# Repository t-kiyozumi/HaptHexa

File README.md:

# HaptHexa
The contents of this repository are the source code and design drawing of a 6-legged robot that can be operated using Dual Shock 3.

#Installation，How to use

Assemble the robot with reference to
HaptHexa / Hardware.

Clone the repository to the computer that controls the robot.

Create a build folder in 
HaptHexa / Software / mainDirectory /

After connecting the dual shock3 controller to the robot's control computer, 
enter the following command to execution

./HaptHexa

Use the left stick to move and the right stick to control the posture.
Pressing select activates the stabilizer and tries to keep the posture horizontal.
In this state, the right stick is used to control the center of gravity.

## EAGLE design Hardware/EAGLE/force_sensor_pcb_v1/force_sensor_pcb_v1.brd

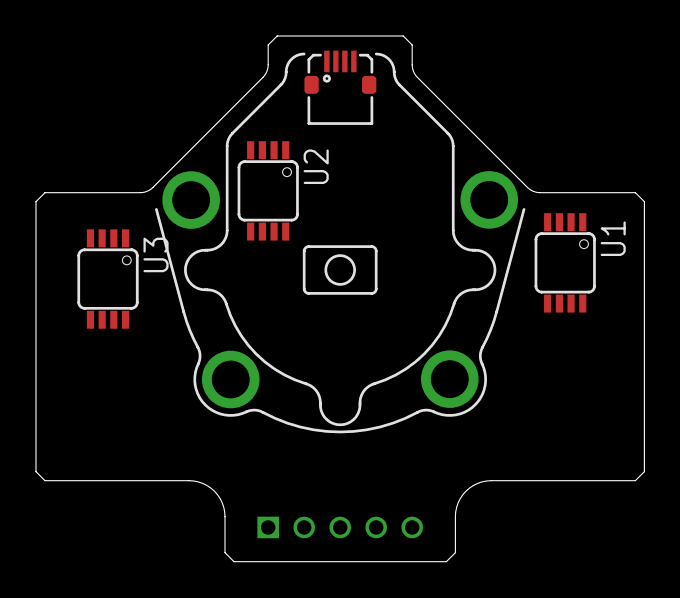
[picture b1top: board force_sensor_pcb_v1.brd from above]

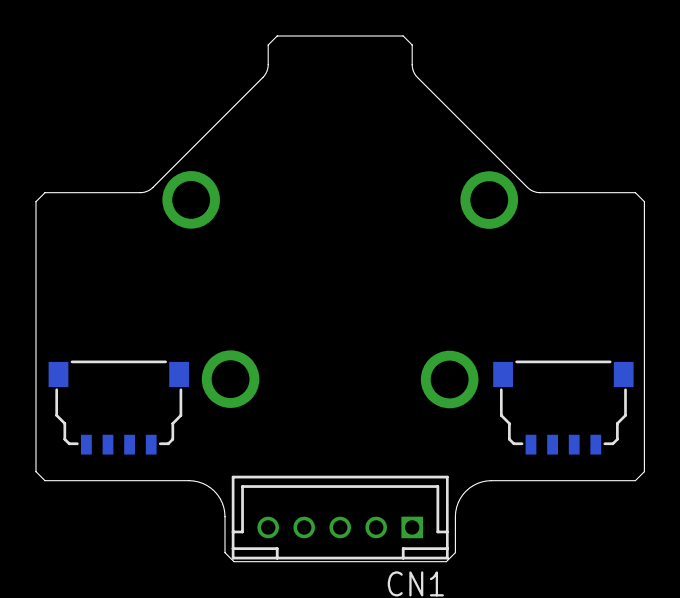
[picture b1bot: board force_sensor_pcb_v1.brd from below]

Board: 2 copper layers, 33.8 x 29.2 mm, 7 parts (3 on the bottom side), 2 nets, no tracks yet.

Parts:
CN1: B5B-PH-K-S
U1, U2, U3: AD623RM-8; MSOP08
U$1: KYOCERA-62774P; KYOCERA-6277-4
U$5, U$6: DF58-4P4P; DF58-4P

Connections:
+V: U1.7, U2.7, U3.7
-V: U1.4, U2.4, U3.4

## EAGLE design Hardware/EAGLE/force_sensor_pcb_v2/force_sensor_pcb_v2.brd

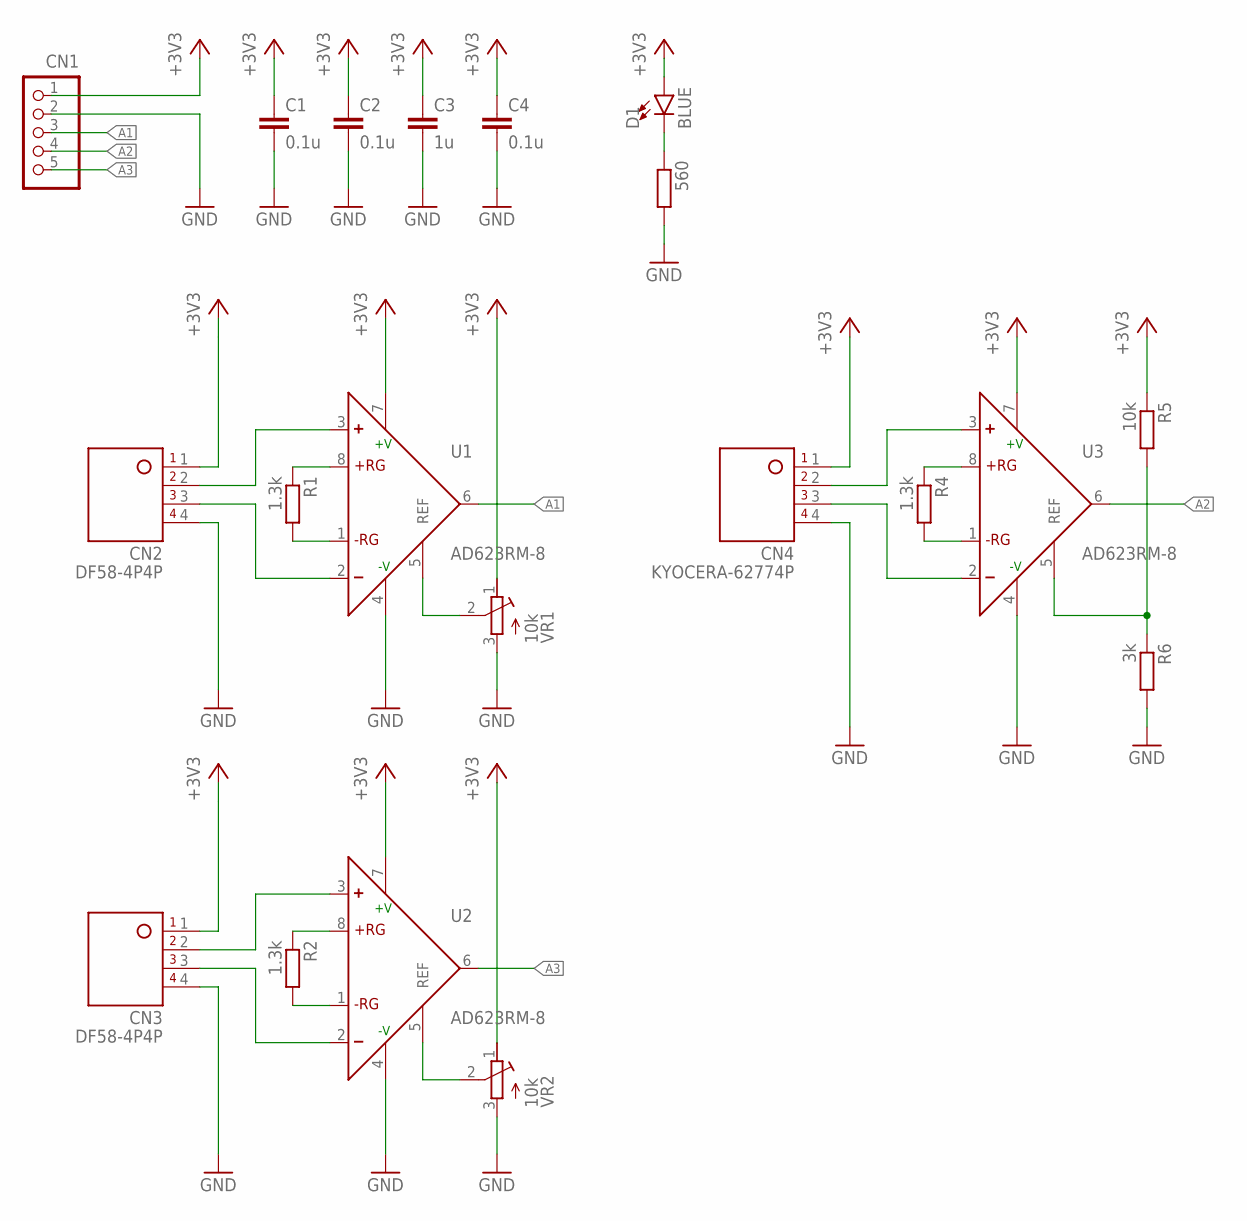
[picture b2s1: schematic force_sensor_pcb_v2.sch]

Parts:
560: R-EU_R0603; R0603
C1, C2, C4: 0.1u; C0603
C3: 1u; C0603
CN1: B5B-PH-K-S
CN2, CN3: DF58-4P4P; DF58-4P
CN4: KYOCERA-62774P; KYOCERA-6277-4
D1: BLUE; LED-0603
R1, R2, R4: 1.3k; R0603
R5: 10k; R0603
R6: 3k; R0603
U1, U2, U3: AD623RM-8; MSOP08
VR1, VR2: 10k; D43A

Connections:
+3V3: C1.1, C2.1, C3.1, C4.1, CN1.1, CN2.1, CN3.1, CN4.1, D1.A, R5.1, U1.7 (+V), U2.7 (+V), U3.7 (+V), VR1.1, VR2.1
A1: CN1.3, U1.6 (OUT)
A2: CN1.4, U3.6 (OUT)
A3: CN1.5, U2.6 (OUT)
GND: 560.2, C1.2, C2.2, C3.2, C4.2, CN1.2, CN2.4, CN3.4, CN4.4, R6.2, U1.4 (-V), U2.4 (-V), U3.4 (-V), VR1.3, VR2.3
unnamed: U1.5 (REF), VR1.2
unnamed: CN2.3, U1.2 (-IN)
unnamed: R1.1, U1.8 (+RG)
unnamed: R1.2, U1.1 (-RG)
unnamed: CN2.2, U1.3 (+IN)
unnamed: R2.1, U2.8 (+RG)
unnamed: U2.5 (REF), VR2.2
unnamed: CN3.3, U2.2 (-IN)
unnamed: CN3.2, U2.3 (+IN)
unnamed: R2.2, U2.1 (-RG)
unnamed: R4.1, U3.8 (+RG)
unnamed: R5.2, R6.1, U3.5 (REF)
unnamed: CN4.3, U3.2 (-IN)
unnamed: CN4.2, U3.3 (+IN)
unnamed: R4.2, U3.1 (-RG)
unnamed: 560.1, D1.C

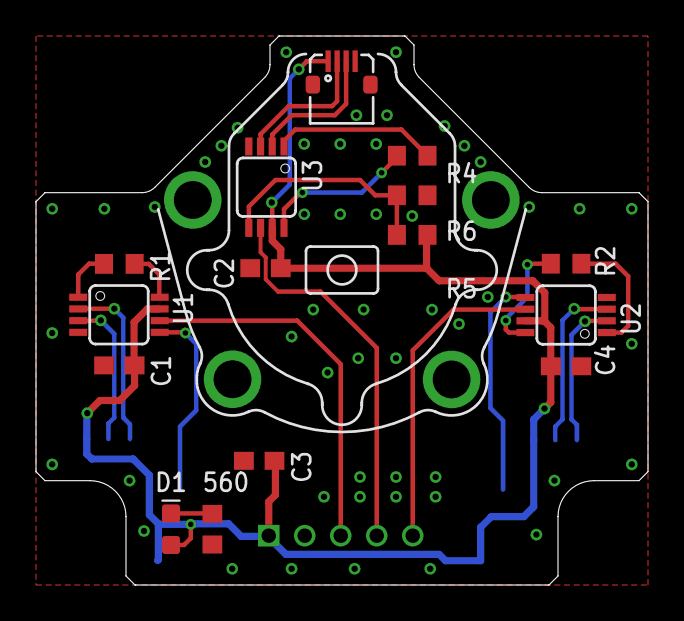
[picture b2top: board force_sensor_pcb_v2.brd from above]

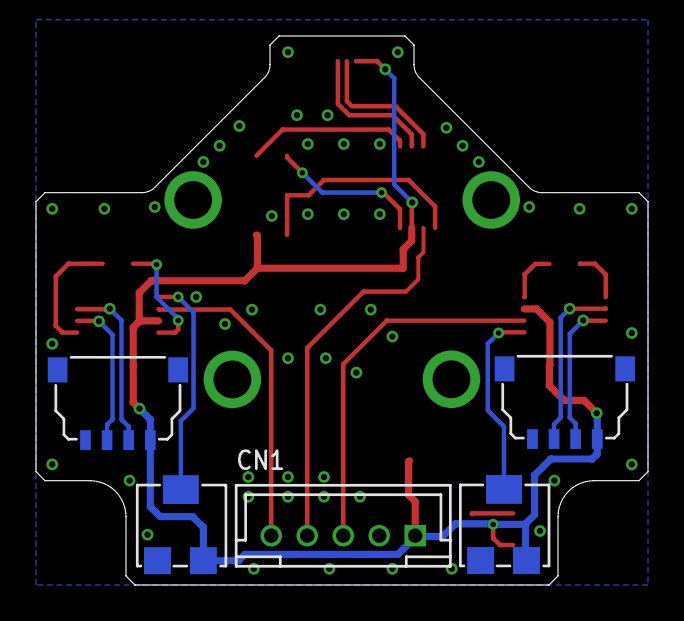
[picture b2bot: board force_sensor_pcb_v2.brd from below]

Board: 2 copper layers, 34.0 x 30.5 mm, 20 parts (5 on the bottom side), 21 nets.

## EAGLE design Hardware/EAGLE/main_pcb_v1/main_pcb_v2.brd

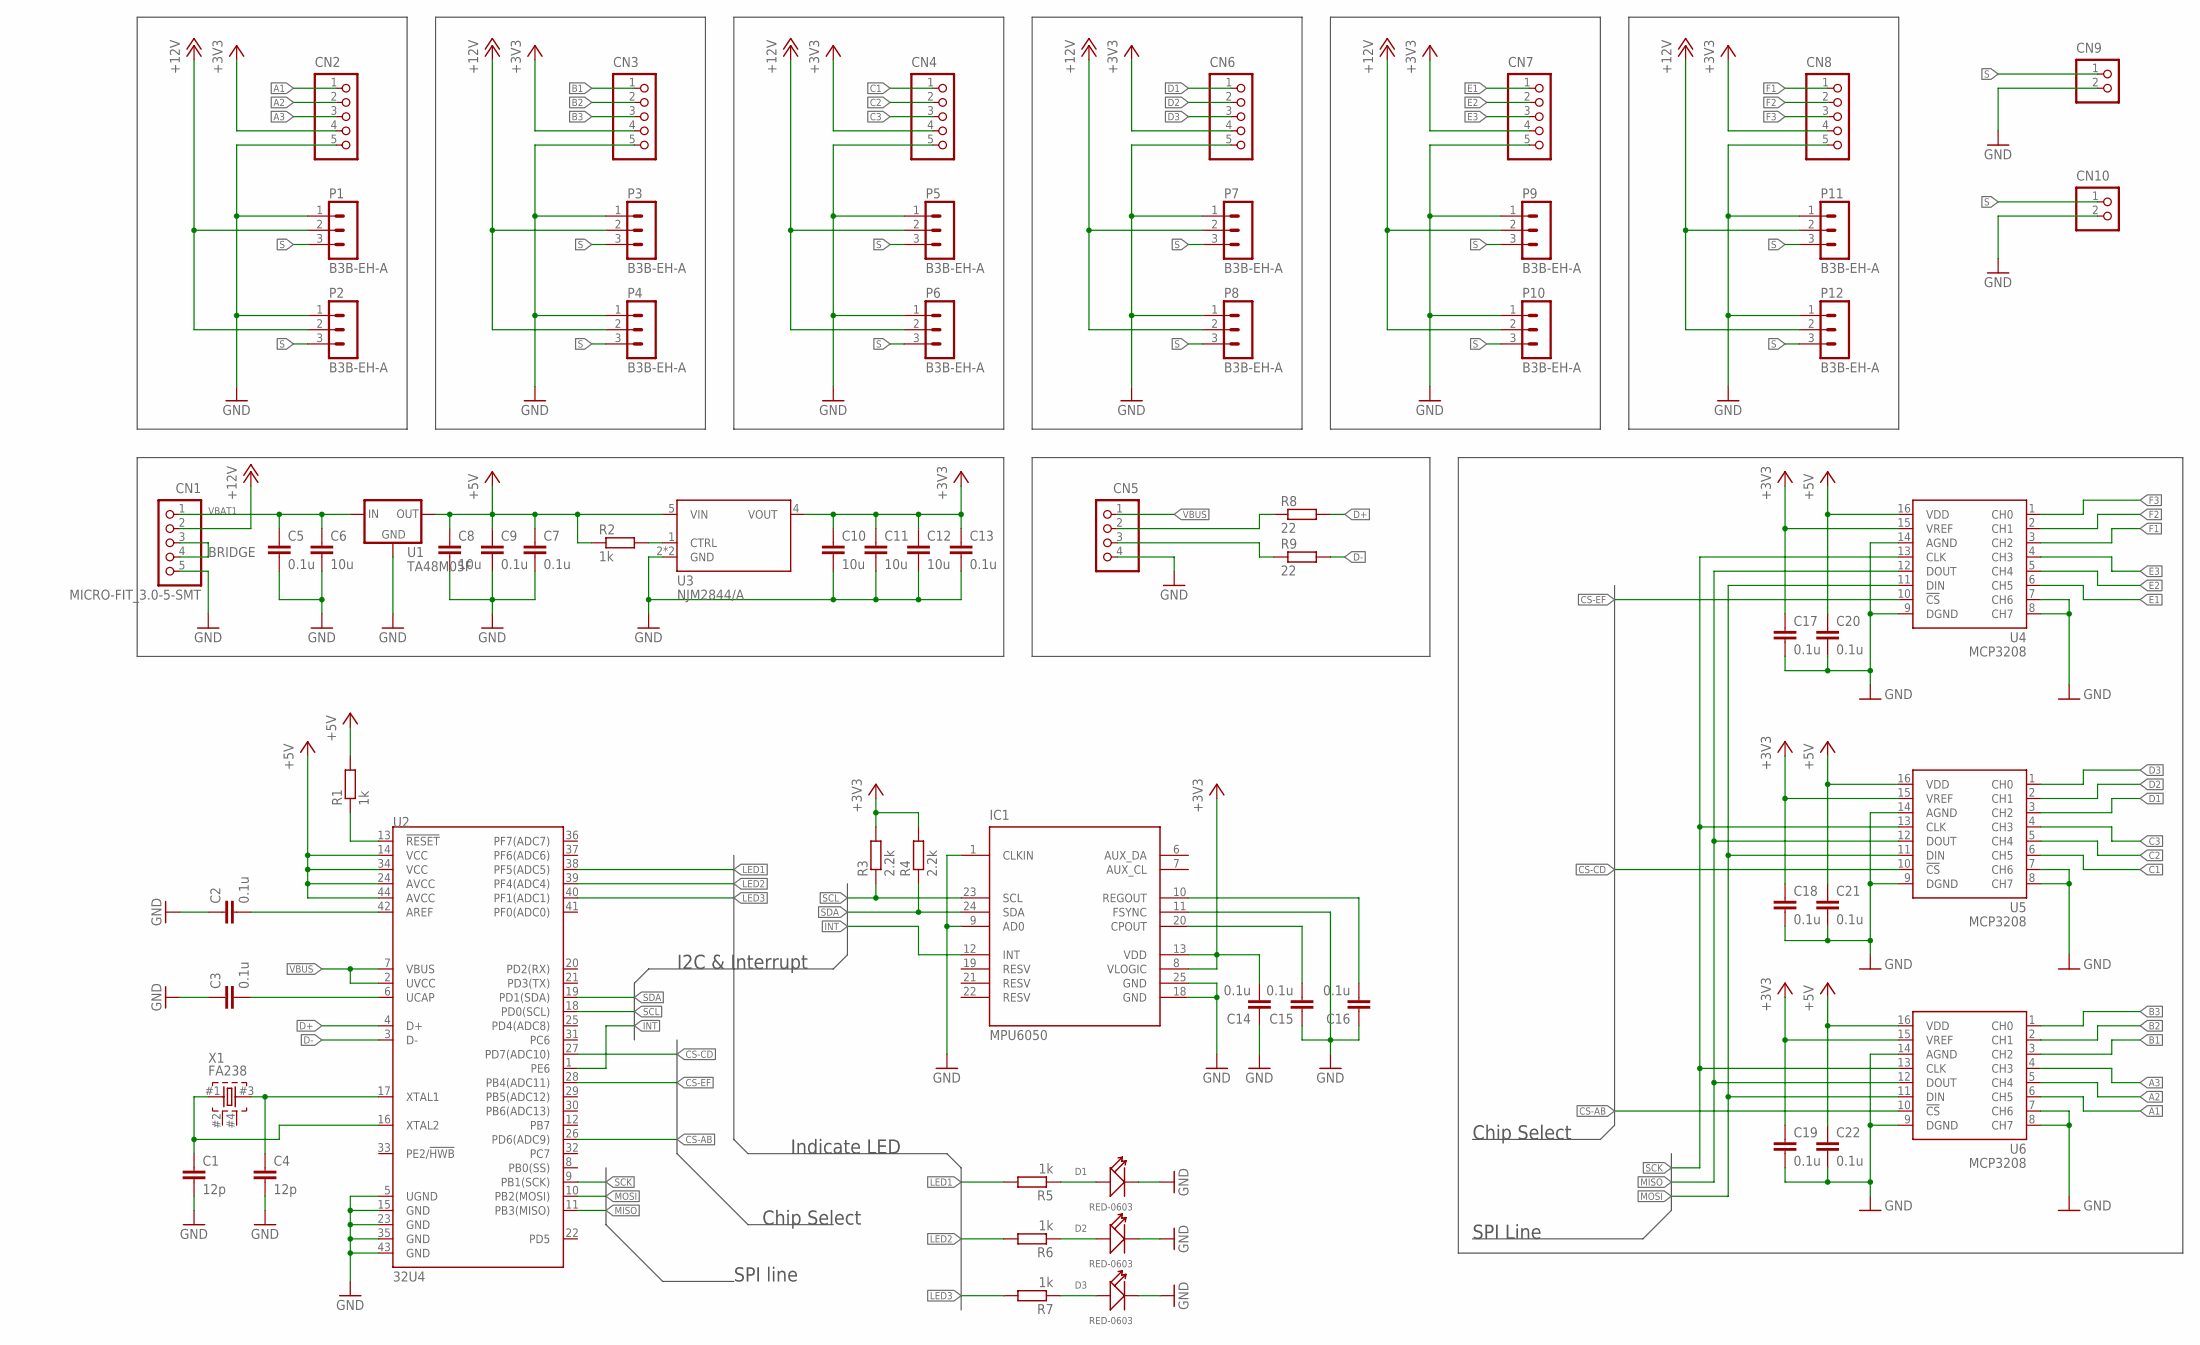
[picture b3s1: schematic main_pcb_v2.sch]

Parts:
C1, C4: 12p; C0603
C2, C3, C5, C7, C9, C13, C14, C15, C16, C17, C18, C19, C20, C21, C22: 0.1u; C0603
C6, C8, C10, C11, C12: 10u; C0805
CN1: MICRO-FIT_3.0-5-SMT; MICRO-FIT_3.0-5_SMT
CN2, CN3, CN4, CN6, CN7, CN8: B5B-PH-K-S
CN5: S4B-PH-K-S
CN9, CN10: B2B-PH-K-S
D1, D2, D3: RED-0603; LED-0603
IC1: MPU6050; QFN50P400X400X95-25T265X275N
P1, P2, P3, P4, P5, P6, P7, P8, P9, P10, P11, P12: B3B-EH-A
R1, R2, R5, R6, R7: 1k; R0603
R3, R4: 2.2k; R0603
R8, R9: 22; R0603
U1: TA48M05F; HSOP3-P-2.30A
U2: 32U4; TQFP44
U3: NJM2844/A; SOT-89-5
U4, U5, U6: MCP3208; SO16
X1: FA238; OSC-FA238

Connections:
+3V3: C10.1, C11.1, C12.1, C13.1, C14.2, C17.1, C18.1, C19.1, CN2.4, CN3.4, CN4.4, CN6.4, CN7.4, CN8.4, IC1.8 (VLOGIC), IC1.13 (VDD), R3.2, R4.2, U3.4 (VOUT), U4.15 (VREF), U5.15 (VREF), U6.15 (VREF)
+5V: C7.1, C8.1, C9.1, C20.1, C21.1, C22.1, R1.2, R2.1, U1.2 (OUT), U2.14 (VCC), U2.24 (AVCC), U2.34 (VCC), U2.44 (AVCC), U3.5 (VIN), U4.16 (VDD), U5.16 (VDD), U6.16 (VDD)
+12V: CN1.2, P1.2, P2.2, P3.2, P4.2, P5.2, P6.2, P7.2, P8.2, P9.2, P10.2, P11.2, P12.2
A1: CN2.1, U6.6 (CH5)
A2: CN2.2, U6.5 (CH4)
A3: CN2.3, U6.4 (CH3)
B1: CN3.1, U6.3 (CH2)
B2: CN3.2, U6.2 (CH1)
B3: CN3.3, U6.1 (CH0)
BRIDGE: CN1.3, CN1.4
C1: CN4.1, U5.6 (CH5)
C2: CN4.2, U5.5 (CH4)
C3: CN4.3, U5.4 (CH3)
CS-AB: U2.26 (PD6(ADC9)), U6.10 (!CS)
CS-CD: U2.27 (PD7(ADC10)), U5.10 (!CS)
CS-EF: U2.28 (PB4(ADC11)), U4.10 (!CS)
D1: CN6.1, U5.3 (CH2)
D2: CN6.2, U5.2 (CH1)
D3: CN6.3, U5.1 (CH0)
D+: R8.2, U2.4 (D+)
D-: R9.2, U2.3 (D-)
E1: CN7.1, U4.6 (CH5)
E2: CN7.2, U4.5 (CH4)
E3: CN7.3, U4.4 (CH3)
F1: CN8.1, U4.3 (CH2)
F2: CN8.2, U4.2 (CH1)
F3: CN8.3, U4.1 (CH0)
GND: C1.2, C2.1, C3.1, C4.2, C5.2, C6.2, C7.2, C8.2, C9.2, C10.2, C11.2, C12.2, C13.2, C14.1, C15.1, C16.1, C17.2, C18.2, C19.2, C20.2, C21.2, C22.2, CN1.5, CN2.5, CN3.5, CN4.5, CN5.4, CN6.5, CN7.5, CN8.5, CN9.2, CN10.2, D1.-, D2.-, D3.-, IC1.1 (CLKIN), IC1.9 (AD0), IC1.11 (FSYNC), IC1.18 (GND), IC1.25 (GND), P1.1, P2.1, P3.1, P4.1, P5.1, P6.1, P7.1, P8.1, P9.1, P10.1, P11.1, P12.1, U1.3 (GND), U2.5 (UGND), U2.15 (GND), U2.23 (GND), U2.35 (GND), U2.43 (GND), U3.2 (GND), U3.2' (GND), U4.7 (CH6), U4.8 (CH7), U4.9 (DGND), U4.14 (AGND), U5.7 (CH6), U5.8 (CH7), U5.9 (DGND), U5.14 (AGND), U6.7 (CH6), U6.8 (CH7), U6.9 (DGND), U6.14 (AGND)
INT: IC1.12 (INT), U2.1 (PE6)
LED1: R5.2, U2.38 (PF5(ADC5))
LED2: R6.2, U2.39 (PF4(ADC4))
LED3: R7.2, U2.40 (PF1(ADC1))
MISO: U2.11 (PB3(MISO)), U4.12 (DOUT), U5.12 (DOUT), U6.12 (DOUT)
MOSI: U2.10 (PB2(MOSI)), U4.11 (DIN), U5.11 (DIN), U6.11 (DIN)
unnamed: CN5.2, R8.1
unnamed: CN5.3, R9.1
unnamed: R2.2, U3.1 (CTRL)
unnamed: C4.1, U2.17 (XTAL1), X1.#3 (3)
unnamed: C1.1, U2.16 (XTAL2), X1.#1 (1)
unnamed: C3.2, U2.6 (UCAP)
unnamed: R1.1, U2.13 (!RESET)
unnamed: C2.2, U2.42 (AREF)
unnamed: C16.2, IC1.10 (REGOUT)
unnamed: D3.+, R7.1
unnamed: C15.2, IC1.20 (CPOUT)
unnamed: D2.+, R6.1
unnamed: D1.+, R5.1
S: CN9.1, CN10.1, P1.3, P2.3, P3.3, P4.3, P5.3, P6.3, P7.3, P8.3, P9.3, P10.3, P11.3, P12.3
SCK: U2.9 (PB1(SCK)), U4.13 (CLK), U5.13 (CLK), U6.13 (CLK)
SCL: IC1.23 (SCL), R3.1, U2.18 (PD0(SCL))
SDA: IC1.24 (SDA), R4.1, U2.19 (PD1(SDA))
VBAT1: C5.1, C6.1, CN1.1, U1.1 (IN)
VBUS: CN5.1, U2.2 (UVCC), U2.7 (VBUS)

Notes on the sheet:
Chip Select
SPI Line
SPI line
Indicate LED
I2C & Interrupt

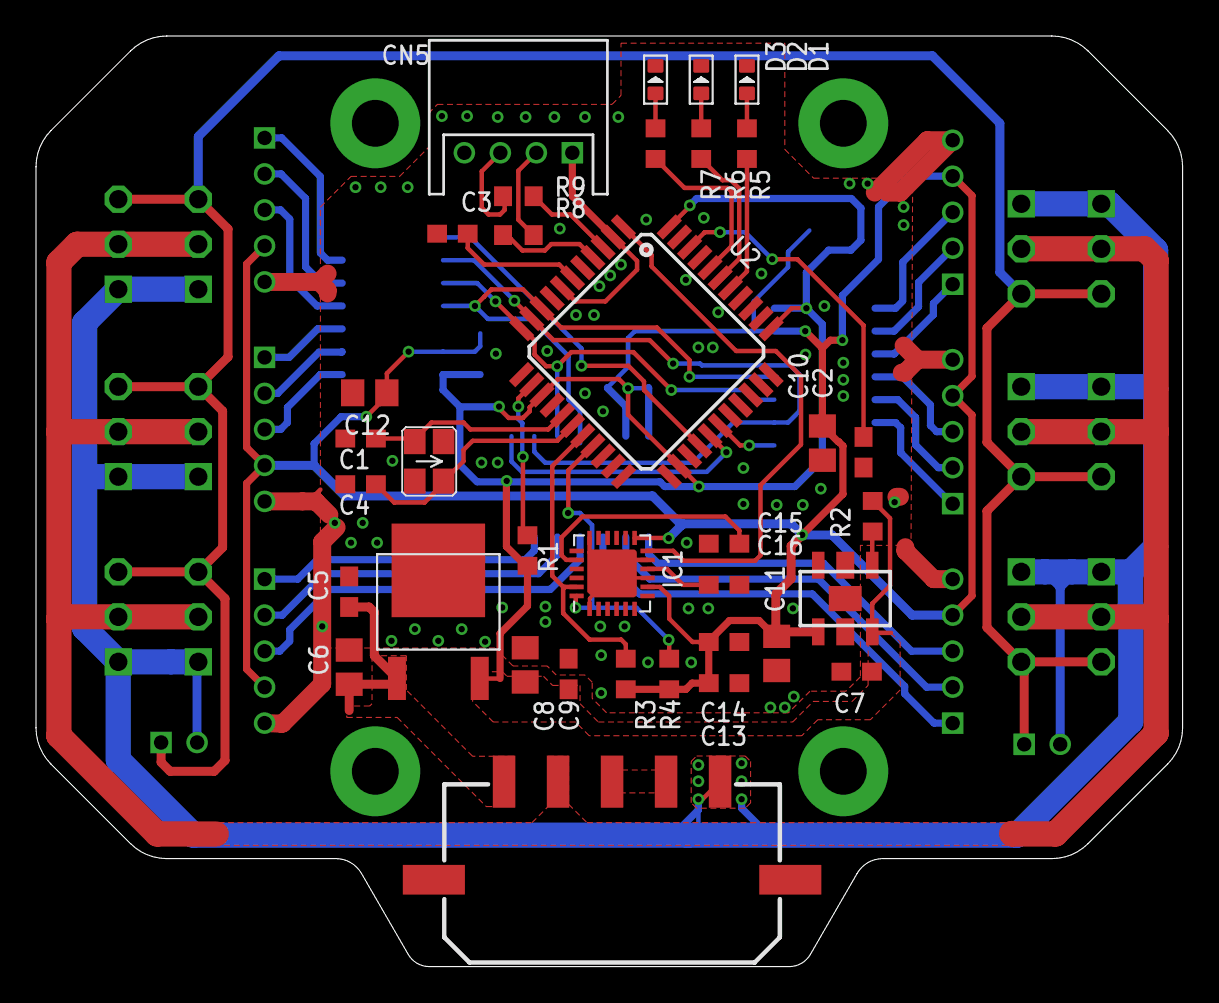
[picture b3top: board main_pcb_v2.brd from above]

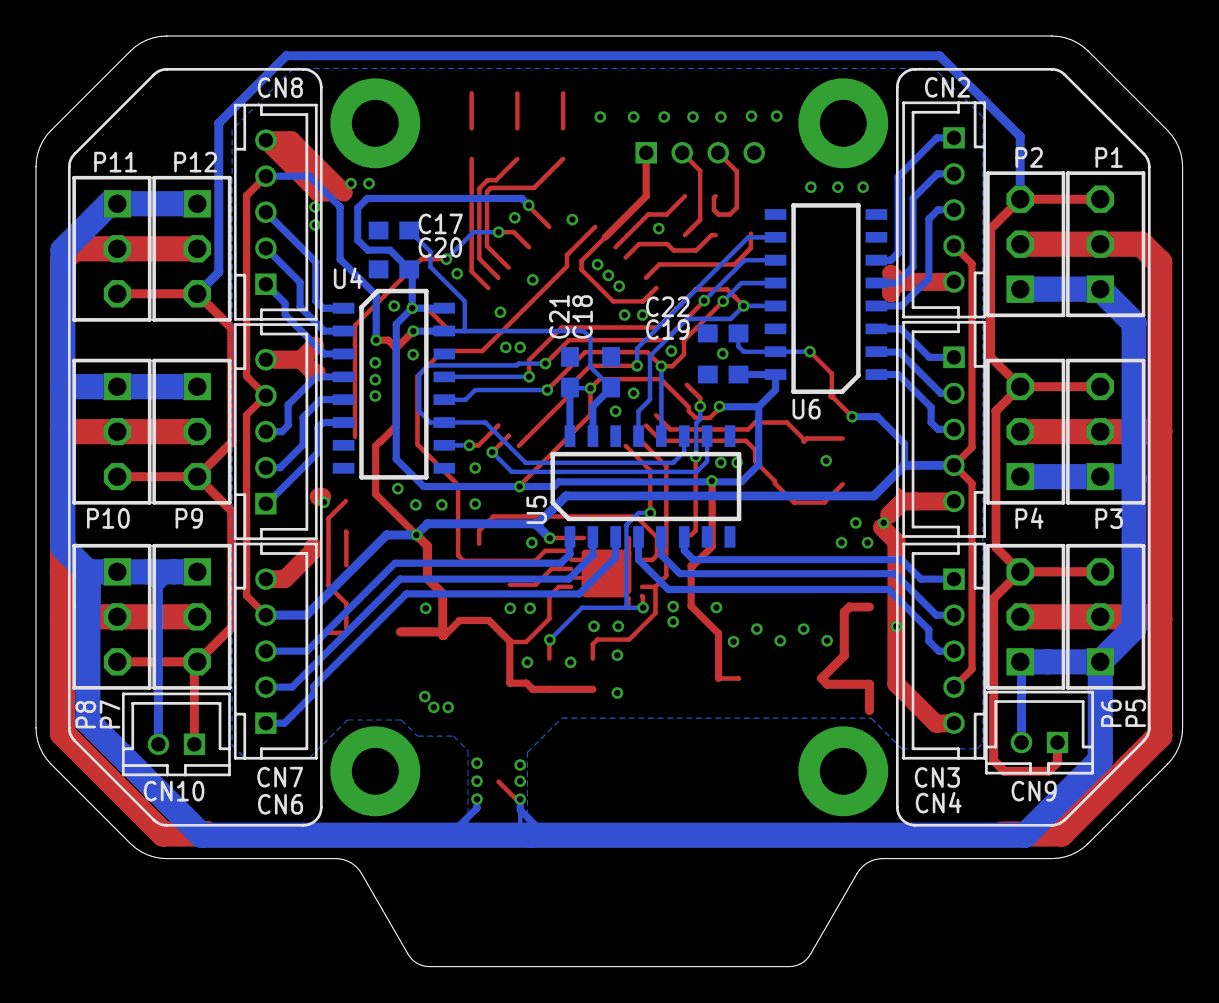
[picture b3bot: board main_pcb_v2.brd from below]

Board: 2 copper layers, 63.7 x 51.7 mm, 64 parts (29 on the bottom side), 53 nets.

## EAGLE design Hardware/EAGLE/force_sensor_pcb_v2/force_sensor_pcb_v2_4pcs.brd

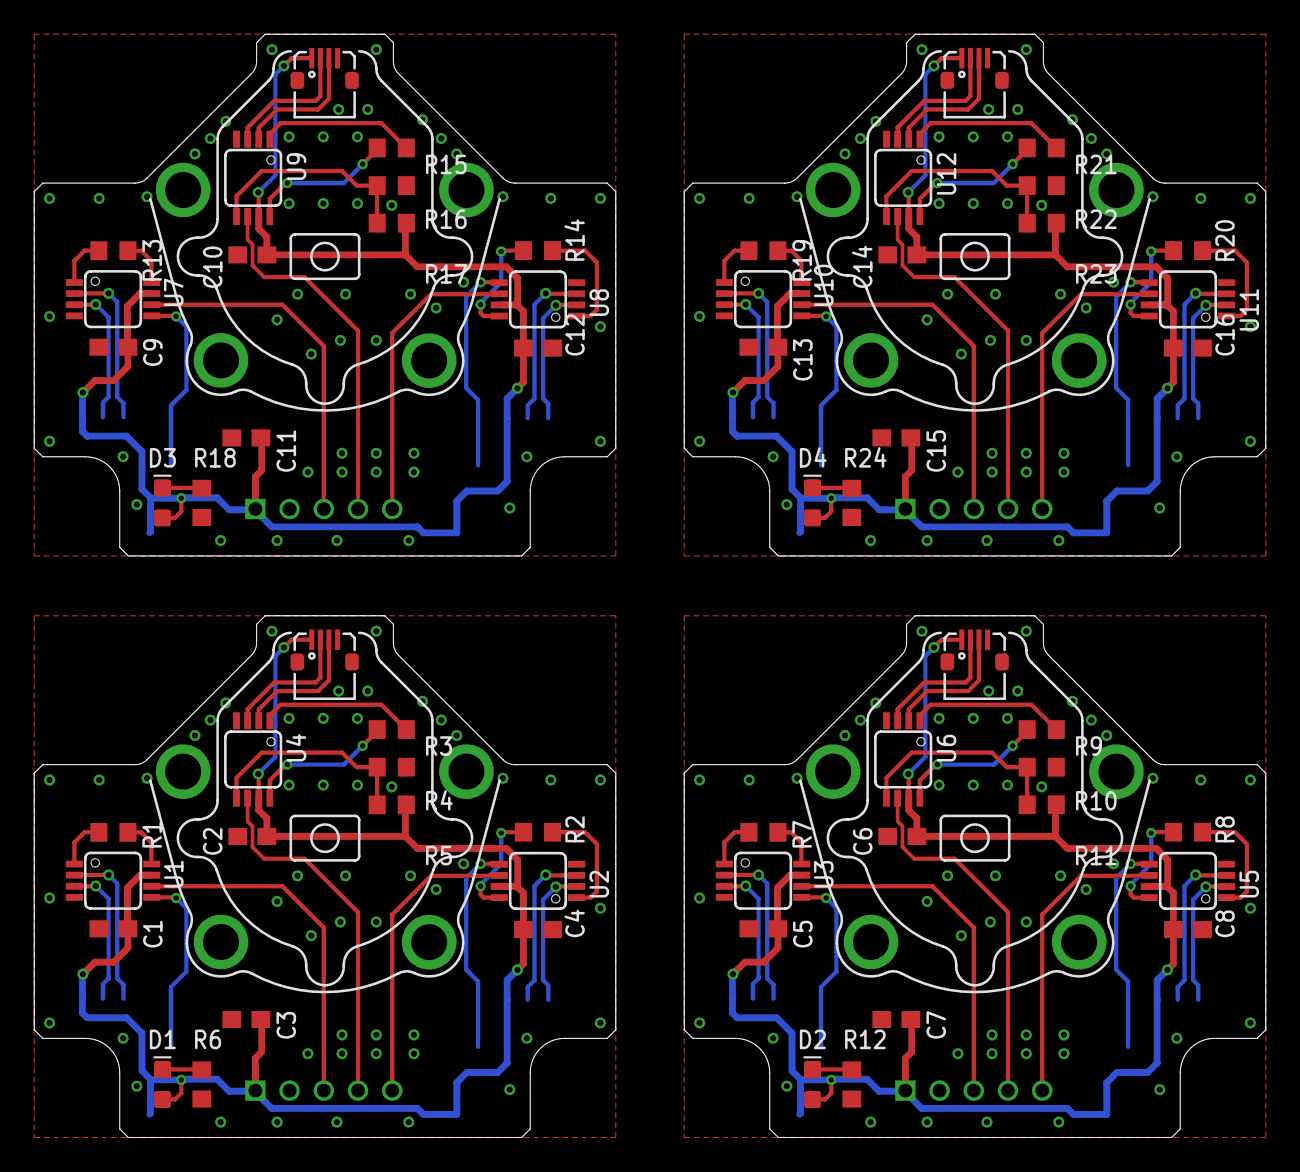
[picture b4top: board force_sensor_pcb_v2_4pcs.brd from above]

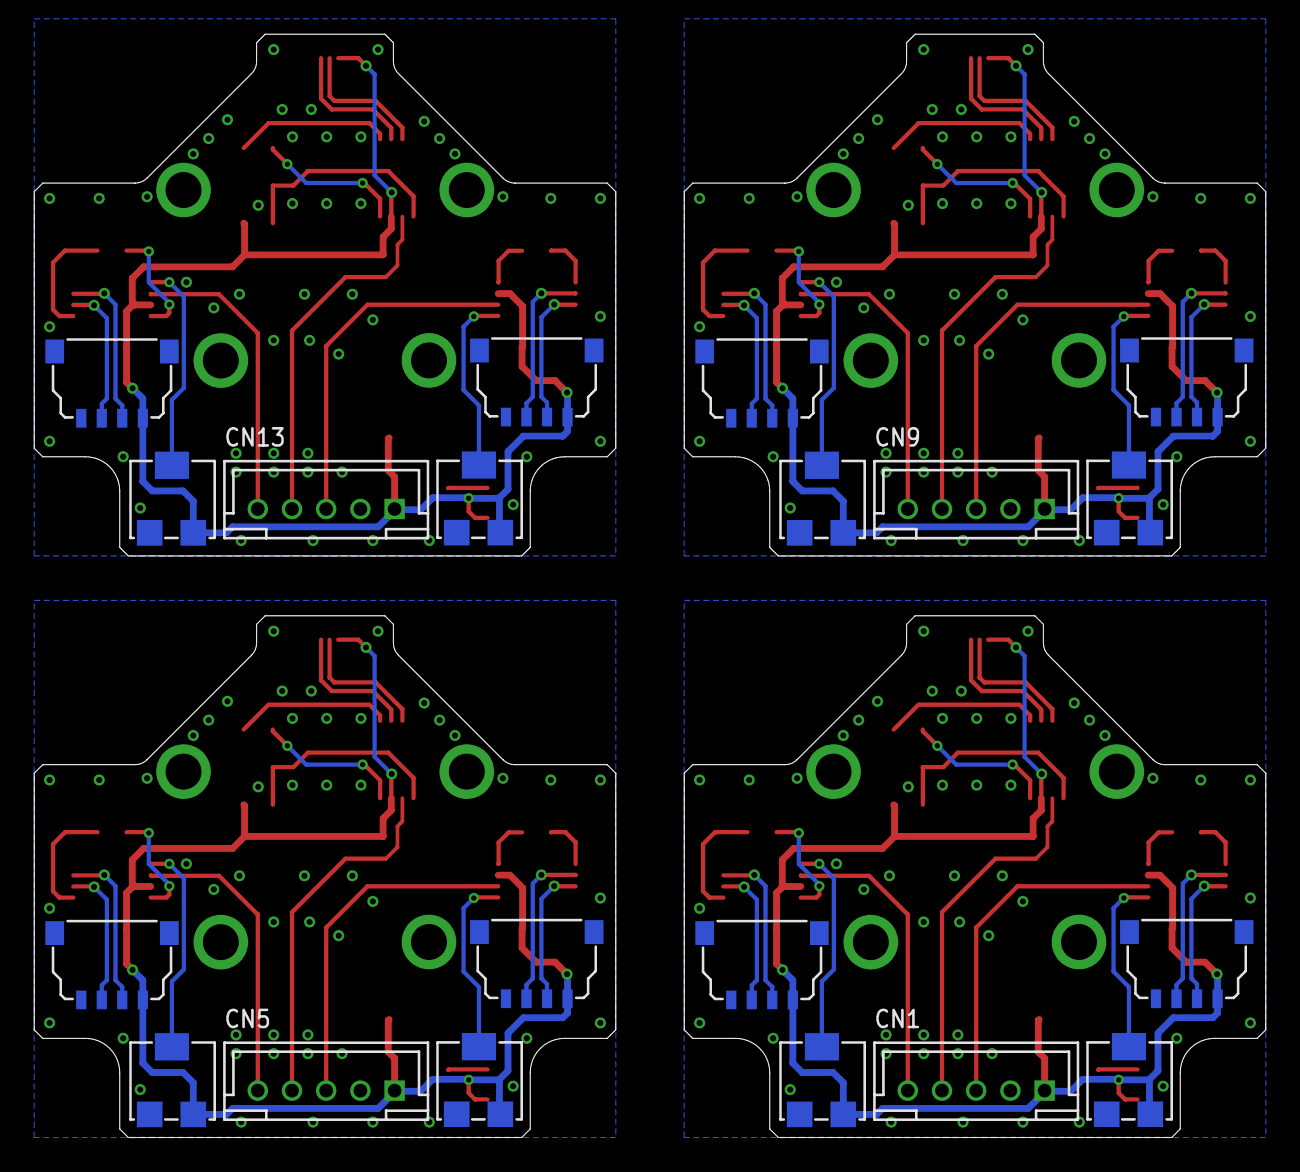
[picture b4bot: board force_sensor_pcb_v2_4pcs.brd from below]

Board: 2 copper layers, 72.0 x 64.5 mm, 80 parts (20 on the bottom side), 84 nets.

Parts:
C1, C2, C3, C4, C5, C6, C7, C8, C9, C10, C11, C12, C13, C14, C15, C16: C0603
CN1, CN5, CN9, CN13: B5B-PH-K-S
CN2, CN3, CN6, CN8, CN10, CN12, CN14, CN16: DF58-4P4P; DF58-4P
CN4, CN7, CN11, CN15: KYOCERA-62774P; KYOCERA-6277-4
D1, D2, D3, D4: BLUE; LED-0603
R1, R2, R6, R7, R8, R12, R13, R14, R18, R19, R20, R24: R0603
R3, R9, R15, R21: 1.3k; R0603
R4, R10, R16, R22: 3k; R0603
R5, R11, R17, R23: 10k; R0603
U1, U2, U3, U4, U5, U6, U7, U8, U9, U10, U11, U12: AD623RM-8; MSOP08
VR1, VR2, VR3, VR4, VR5, VR6, VR7, VR8: D43A

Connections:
+3V1: C5.1, C6.1, C7.1, C8.1, CN5.1, CN6.1, CN7.1, CN8.1, D2.A, R11.1, U3.7, U5.7, U6.7, VR3.1, VR4.1
+3V2: C9.1, C10.1, C11.1, C12.1, CN9.1, CN10.1, CN11.1, CN12.1, D3.A, R17.1, U7.7, U8.7, U9.7, VR5.1, VR6.1
+3V3: C1.1, C2.1, C3.1, C4.1, CN1.1, CN2.1, CN3.1, CN4.1, D1.A, R5.1, U1.7, U2.7, U4.7, VR1.1, VR2.1
+3V4: C13.1, C14.1, C15.1, C16.1, CN13.1, CN14.1, CN15.1, CN16.1, D4.A, R23.1, U10.7, U11.7, U12.7, VR7.1, VR8.1
A1: CN1.3, U1.6
A2: CN1.4, U4.6
A3: CN1.5, U2.6
A4: CN5.3, U3.6
A5: CN5.4, U6.6
A6: CN5.5, U5.6
A7: CN9.3, U7.6
A8: CN9.4, U9.6
A9: CN9.5, U8.6
A10: CN13.3, U10.6
A11: CN13.4, U12.6
A12: CN13.5, U11.6
GND: C1.2, C2.2, C3.2, C4.2, CN1.2, CN2.4, CN3.4, CN4.4, R4.2, R6.2, U1.4, U2.4, U4.4, VR1.3, VR2.3
GND1: C5.2, C6.2, C7.2, C8.2, CN5.2, CN6.4, CN7.4, CN8.4, R10.2, R12.2, U3.4, U5.4, U6.4, VR3.3, VR4.3
GND2: C9.2, C10.2, C11.2, C12.2, CN9.2, CN10.4, CN11.4, CN12.4, R16.2, R18.2, U7.4, U8.4, U9.4, VR5.3, VR6.3
GND3: C13.2, C14.2, C15.2, C16.2, CN13.2, CN14.4, CN15.4, CN16.4, R22.2, R24.2, U10.4, U11.4, U12.4, VR7.3, VR8.3
unnamed: U1.5, VR1.2
unnamed: CN2.3, U1.2
unnamed: R1.1, U1.8
unnamed: R1.2, U1.1
unnamed: CN2.2, U1.3
unnamed: R2.1, U2.8
unnamed: U2.5, VR2.2
unnamed: CN3.3, U2.2
unnamed: CN3.2, U2.3
unnamed: R2.2, U2.1
unnamed: R3.1, U4.8
unnamed: R4.1, R5.2, U4.5
unnamed: CN4.3, U4.2
unnamed: CN4.2, U4.3
unnamed: R3.2, U4.1
unnamed: D1.C, R6.1
unnamed: R7.1, U3.8
unnamed: U3.5, VR3.2
unnamed: CN6.3, U3.2
unnamed: CN6.2, U3.3
unnamed: R7.2, U3.1
unnamed: R8.1, U5.8
unnamed: U5.5, VR4.2
unnamed: CN8.3, U5.2
unnamed: CN8.2, U5.3
unnamed: R8.2, U5.1
unnamed: R9.1, U6.8
unnamed: R10.1, R11.2, U6.5
unnamed: CN7.3, U6.2
unnamed: CN7.2, U6.3
unnamed: R9.2, U6.1
unnamed: D2.C, R12.1
unnamed: R13.1, U7.8
unnamed: U7.5, VR5.2
unnamed: CN10.3, U7.2
unnamed: CN10.2, U7.3
unnamed: R13.2, U7.1
unnamed: R14.1, U8.8
unnamed: U8.5, VR6.2
unnamed: CN12.3, U8.2
unnamed: CN12.2, U8.3
unnamed: R14.2, U8.1
unnamed: R15.1, U9.8
unnamed: R16.1, R17.2, U9.5
unnamed: CN11.3, U9.2
unnamed: CN11.2, U9.3
unnamed: R15.2, U9.1
unnamed: D3.C, R18.1
unnamed: R19.1, U10.8
unnamed: U10.5, VR7.2
unnamed: CN14.3, U10.2
unnamed: CN14.2, U10.3
unnamed: R19.2, U10.1
unnamed: R20.1, U11.8
unnamed: U11.5, VR8.2
unnamed: CN16.3, U11.2
unnamed: CN16.2, U11.3
unnamed: R20.2, U11.1
unnamed: R21.1, U12.8
unnamed: R22.1, R23.2, U12.5
unnamed: CN15.3, U12.2
unnamed: CN15.2, U12.3
unnamed: R21.2, U12.1
unnamed: D4.C, R24.1

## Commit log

2019-12-10 静止状態の姿勢を制御するプログラムを追加、ヨー、ピッチ、ロール、支持正六角形の辺の大きさなどのパラメータから脚の位置を計算できる
2019-12-10 動作合成について修正，ベクトル合成の方法が間違っていたので直した，位置を絶対位置ではなく前の位置からの相対位置で指定するようにした
2019-12-10 Add gitignore & gitattributes
2019-12-10 Change directory structure, devide Hardware & Software onth two different locations
2019-12-10 Add inventor cad fil & EAGLE pcb design file
2020-01-23 Reorganized repository structure.
2020-01-23 Added auto balancer with gyro sensor
2020-01-24 Added a program to control the center of gravity manually in the auto mode
2020-01-24 The names of each mode have been changed for clarity
2020-01-24 Added height adjustment function by controller
2020-01-24 Added the function to change the size of the support polygon by the controller
2020-01-29 added function that log body angle
2020-02-05 Added the function to record the time
2020-02-06 Adjusted proportional gain
2020-02-06 Implemented PI control
2020-02-07 Adjusted PD gain
2020-02-07 Added markers to organize experiment results
2020-02-11 Remove "Computer" from main assembly, Add UCS on each assembly.
2020-02-28 addjusuted PI gain
2020-02-28 swithch the contoroll system
2021-05-29 Update parts numbering

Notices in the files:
parts and their libraries:
con-jst-eh: Copyright (C) 2016, Bob Starr
